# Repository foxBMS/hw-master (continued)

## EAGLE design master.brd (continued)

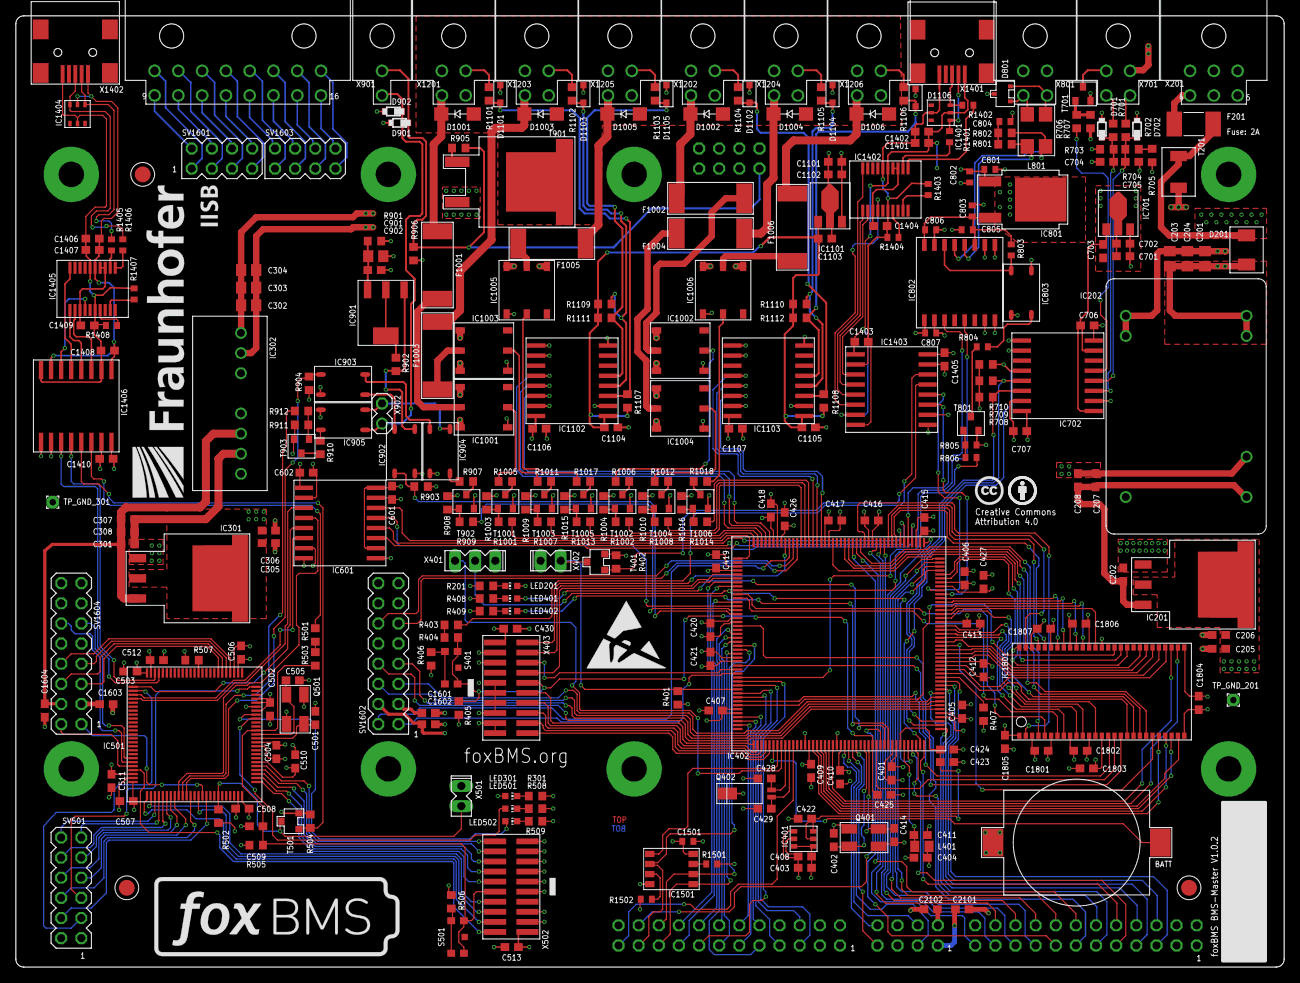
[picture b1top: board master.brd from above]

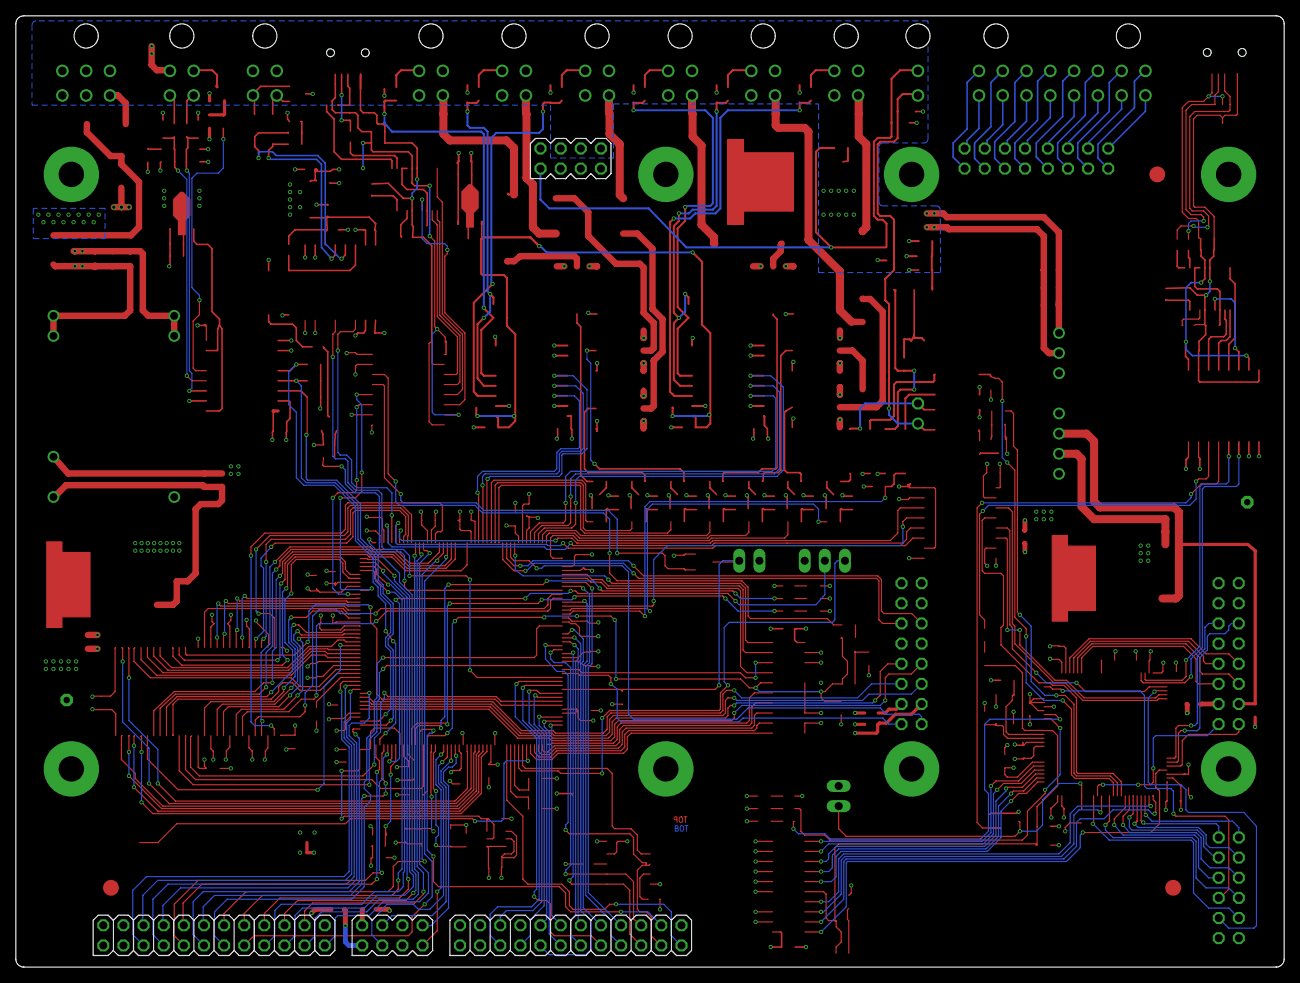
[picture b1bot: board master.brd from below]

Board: 4 copper layers, 160.0 x 120.0 mm, 318 parts (4 on the bottom side), 331 nets.

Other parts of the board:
U$1, U$3, U$4: FIDUCIAL_1MM
U$2: ESD_10.00

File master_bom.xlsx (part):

| Pos | Populate | Qty | Value | Device | Package | Parts | Description | Farnell | Digikey | Mouser
Resistor
 | 1 | yes | 9 | 0 | R-EU_R0603 | R0603 | R403 R406 R501 R506 R705 R1403 R1404 R1407 R1408 | RESISTOR, European symbol | 2059527
 | 2 | yes | 2 | 1.5k | R-EU_R0603 | R0603 | R701 R702 | RESISTOR, European symbol | 2303156
 | 3 | yes | 12 | 10 | R-EU_R0603 | R0603 | R706 R901 R905 R909 R912 R1001 R1002 R1007 R1008 R1013 R1014 R806 | RESISTOR, European symbol | 2302958
 | 4 | yes | 32 | 10k | R-EU_R0603 | R0603 | R401 R402 R405 R407 R502 R504 R505 R507 R707 R708 R709 R710 R903 R904 R908 R911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 | RESISTOR, European symbol | 2303192
 | 5 | yes | 1 | 120 | R-EU_R0603 | R0603 | R902 | RESISTOR, European symbol | 2303067
 | 6 | yes | 6 | 130 | R-EU_R0603 | R0603 | R201 R301 R408 R409 R508 R509 | RESISTOR, European symbol | 2059288
 | 7 | yes | 8 | 430 | R-EU_R0603 | R0603 | R907 R910 R1005 R1006 R1011 R1012 R1017 R1018 R804 | RESISTOR, European symbol | 2145386
 | 8 | yes | 1 | 330 | R-EU_R0603 | R0603 | R906 | RESISTOR, European symbol | 2145370
 | 9 | yes | 4 | 27 | R-EU_R0603 | R0603 | R1401 R1402 R1405 R1406 | RESISTOR, European symbol | 2145363
 | 10 | yes | 6 | 47 | R-EU_R0603 | R0603 | R1101 R1102 R1103 R1104 R1105 R1106 | RESISTOR, European symbol | 2145397
 | 11 | yes | 2 | 62 | R-EU_R0603 | R0603 | R801 R802 | RESISTOR, European symbol | 2303039
 | 12 | yes | 4 | 680 | R-EU_R0603 | R0603 | R404 R503 R703 R704 | RESISTOR, European symbol | 2303131
Capacitor
 | 13 | yes | 74 | 100n | C-EUC0603 | C0603 | C202 C206 C208 C301 C306 C308 C401 C404 C405 C406 C407 C408 C409 C410 C411 C412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 | CAPACITOR, European symbol | 1828890
 | 14 | yes | 4 | 100n 50V | C-EUC0604 | C0603 | C702 C802 C902 C1102 | CAPACITOR, European symbol | 2346967
 | 15 | yes | 8 | 18p | C-EUC0605 | C0603 | C402 C414 C428 C429 C501 C505 C704 C705 | CAPACITOR, European symbol | 2070403
 | 16 | yes | 6 | 1µ | C-EUC0606 | C0603 | C205 C207 C305 C307 C403 C423 | CAPACITOR, European symbol | 1907343
 | 17 | yes | 3 | 1µ 35V | C-EUC0607 | C0603 | C701 C801 C1101 | CAPACITOR, European symbol | 2346909
 | 18 | yes | 4 | 2.2µ | C-EUC0608 | C0603 | C426 C427 C511 C512 | CAPACITOR, European symbol | 2346961
 | 19 | yes | 7 | 2.2µ 50V | C-EUC0609 | C0805 | C201 C203 C204 C302 C303 C304 C901 | CAPACITOR, European symbol | 2346945
 | 20 | yes | 2 | 4.7µ | C-EUC0610 | C0603 | C1401 C1406 | CAPACITOR, European symbol | 2362098
L
 | 21 | yes | 1 |  | L0805 | 0805 | L401 |  | 2443249
 | 22 | yes | 1 |  | B82789N | B82789N | L801 |  |  |  | 871-B82789C513N2
LED
 | 23 | yes | 2 | Green | LEDCHIP-LED0603 | CHIP-LED0603 | LED402 LED502 | LED | 2099223
 | 24 | yes | 2 | Red | LEDCHIP-LED0603 | CHIP-LED0603 | LED401 LED501 | LED | 2099221
 | 25 | yes | 2 | Orange | LEDCHIP-LED0603 | CHIP-LED0603 | LED201 LED301 | LED | 2099222
XTAL
 | 26 | yes | 2 | 7B-8.000MAAJ-T | 7B-8.000MAAJ-T | MJ | Q401 Q501 | MJ Quarz, 5 x 3.2 x 1.0mm SMD | 2308726
 | 27 | yes | 1 |  | MS3V | MS3V-T1R | Q402 |  | 1539368
Transistor
 | 28 | yes | 2 | BSS84P | BSS84P | SOT23 | T401 T501 | #2245 | 1056526
 | 29 | yes | 1 | BUK964R8-60E | BUK964R8-60E | TO-263AB | T901 | #2797 N-Channel PowerTrench MOSFET 60V, 75A 10.5mOhm | 2254205
 | 30 | yes | 10 | IRLML0100TRPBF | IRLML0100TRPBF | SOT-23 | T701 T801 T902 T903 T1001 T1002 T1003 T1004 T1005 T1006 |  | 1783928
IC
 | 31 | yes | 1 | ADR3425 | ADR3425 | SOT23-6 | IC401 | Micropower, high accuracy, voltage references | 2377039
 | 32 | yes | 2 | ADUM3300 | ADUM3300 | SO-16W | IC1102 IC1103 | Triple-Channel Digital Isolators | 2409432
 | 33 | yes | 1 | ADUM3301 | ADUM3301 | SO-16W | IC702 | Triple-Channel Digital Isolators | 2462515
 | 34 | yes | 3 | ADUM3401 | ADUM3401 | SO16W | IC601 IC1403 IC1406 | Analog Devices Magnetkoppler 4-Kanal | 1274129
 | 35 | yes | 2 | FT231XS-R | FT231XS-R | IC_SMD_SSOP-20 | IC1402 IC1405 | FT231X?-* - FTDI | 2081328
 | 36 | yes | 1 | AT25128B-SSHL-T | AT25128B-SSHL-T | SO8 | IC1501 | SPI bus serial EEPROM | 2345601
 | 37 | yes | 1 | TJA1052IT/5Y | TJA1052IT/5Y | SO16W | IC802 |  | 2400552
Diode
 | 38 | yes | 1 | PESD1CAN | PESD1CAN | SOT-23_NEU | D801 | NXP PESD1CAN CAN bus ESD protection diode | 1510703
 | 39 | yes | 1 | STPS3L60U | STPS3L60U | SMB | D201 | Schottky Diode | 9907769
 | 40 | yes | 2 | MM3Z12VT1G | MM3Z12VT1G | SOD323 | D901 D902 | MM3Z_xVx_T1 Series Zener Diode | 1431191
 | 41 | yes | 6 | CDSOD323-T05 | CDSOD323-T05 | SOD323 | D1101 D1102 D1103 D1104 D1105 D1106 | TVS CDSOD323-T05 | 2341914
 | 42 | yes | 2 | MM3Z4V7ST1G | MM3Z4V7ST1G | SOD323 | D701 D702 | MM3Z_xVx_T1 Series Zener Diode | 2463512
 | 43 | no | 6 | GF1B | GF1B | SMA-DO214AC | D1001 D1002 D1003 D1004 D1005 D1006 | DIODE | 1467477
MCU
 | 44 | yes | 1 | STM32F429IIT6 | STM32F429IIT6 | LQFP176 | IC402 | ARM 32-bit Cortex™-M3 CPU |  | 497-14054-ND
 | 45 | yes | 1 | STM32F429VIT6 | STM32F429VGT6 | LQFP100 | IC501 | ARM 32-bit Cortex™-M3 CPU | 2393659
Regulator
 | 46 | yes | 1 | KA7805ERTF | KA7805ERTF | TO252 | IC801 | Positive VOLTAGE REGULATOR | 2102585
 | 47 | yes | 2 | UA78L05CPK | UA78L05CPK | SOT89 | IC701 IC1101 | POSITOIV-VOLTAGE REGULATORS | 2112604
 | 48 | yes | 2 | LM1085-3.3 | LM1085-3.3 | TO-263-3L | IC201 IC301 | National Semiconductor LM1085IS-5 3A Low Dropout Positive Regulators | 1469039
 | 49 | yes | 1 | LM317MSTT3 | LM317MSTT3 | SOT223 | IC901 | 500 mA Adjustable Output Positive Voltage Regulator | 1703412
Opto
 | 50 | yes | 6 | AQV252G2SX | AQV252G2SX | SOP06 | IC1001 IC1002 IC1003 IC1004 IC1005 IC1006 |  |  | 255-3594-1-ND
 | 51 | yes | 5 | CPC1008N | CPC1008N | SOP4 | IC803 IC902 IC903 IC904 IC905 | CLARE - Single-Pol, Normally Open 4-Pin SOP OptoMOS Relay, 150mA load current | 1653755
Misc
 | 52 | yes | 1 | SMTU 1225-1-LF | SMTU 1225-1-LF | CR1225_SMD | BATT | #2833 | 1216353
 | 53 | yes | 2 | MC32598 | MC32598 | Mini-USB AB | X1401 X1402 | MINI USB-B Conector | 1696539
 | 54 | yes | 2 | IP4220CZ6 | IP4220CZ6 | TSOP-6 | IC1401 IC1404 |  | 1506629
 | 55 | yes | 1 | IS42S16400J-7TLI | IS42S16400J-7TLI | TSOP-54 | IC1801 |  | 2253831
 | 56 | yes | 2 | KMR211G | KMR211G | KMR211G | S401 S501 | #228 |  | 401-1426-1-ND
 | 57 | yes | 6 | 4,0A_UMT | 4,0A_UMT | F_SMD_11,00MMX3,00MMX3,00MM_(UMT)_R_SCHURTER_REV01 | F1001 F1002 F1003 F1004 F1005 F1006 | UMT-Serie - Schurter Electronic Components |  | 486-1253-ND | 693-3403.0172.11
 | 58 | yes | 1 | 2A | Littelfuse 452 | NANO2 | F201 | 452 Serie Littelfuse | 2383284
 | 59 | yes | 1 | TISP4040H1BJR-S | TISP4040H1BJR-S | SMBJ | T201 | TVS Thyristor |  | TISP4040H1BJR-SCT-ND
Connector SMD
 | 60 | yes | 2 | FTS-110-01-L-DV | FTS-110-01-L-DV | FTS-110-01-L-DV | X403 X502 | SAMTEC connector, #537 | 1667733
Connector THD
 | 61 | yes | 1 | HEADER_POS16_43045-1599 | HEADER_POS16_43045-1600 | 43045-1600 | X1601 | Molex - Micro-Fit 3.0 Series connector, 3.00mm (0.118) pitch header, 16 positio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 | 9961380
 | 62 | yes | 1 | HEADER_POS2_43045-0199 | HEADER_POS2_43045-0200 | 43045-0200 | X901 | Molex - Micro-Fit 3.0 Series connector, 3.00mm (0.118) pitch header, 2 position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 | 1012251
 | 63 | yes | 8 | HEADER_POS4_43045-0400 | HEADER_POS4_43045-0401 | 43045-0400 | X701 X801 X1201 X1202 X1203 X1204 X1205 X1206 | Molex - Micro-Fit 3.0 Series connector, 3.00mm (0.118) pitch header, 4 position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 | 9733019
 | 64 | yes | 1 | HEADER_POS6_43045-0599 | HEADER_POS6_43045-0600 | 43045-0600 | X201 | Molex - Micro-Fit 3.0 Series connector, 3.00mm (0.118) pitch header, 6 position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 | 1012252
 | 65 | yes | 1 | MA03-0 | MA03-1 | MA03-1 | X401 | 3Pins | 2505045
 | 66 | yes | 1 |  |  |  | SV901 | 8 Header | 1668094
 | 67 | yes | 3 | MA04-1 | MA04-2 | MA04-2 | SV1601 SV1603 SV2101 | 8 Pins | 2025250
 | 68 | yes | 1 | MA06-1 | MA06-2 | MA06-2 | SV501 | 12 Pins | 2025252
 | 69 | yes | 2 | MA08-1 | MA08-2 | MA08-2 | SV1602 SV1604 | 16 Pins | 2025254
 | 70 | no | 1 | MA02-0 | MA02-0 | MA02-0 | X902 | 1 Pins | 2505044
 | 71 | yes | 2 | MA02-1 | MA02-1 | MA02-1 | X402 X501 | 2 Pins | 2505044
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
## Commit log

2017-12-13 Initial commit of the hardware design resources for the foxBMS Master board
2017-12-13 fixed fuse value in schematic
2017-12-13 fixed README.md
